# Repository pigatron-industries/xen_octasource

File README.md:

# OctaSource

A Eurorack synthesiser module with 8 control voltage outputs.

[Documentation](https://pigatron-industries.github.io/xen_octasource/)

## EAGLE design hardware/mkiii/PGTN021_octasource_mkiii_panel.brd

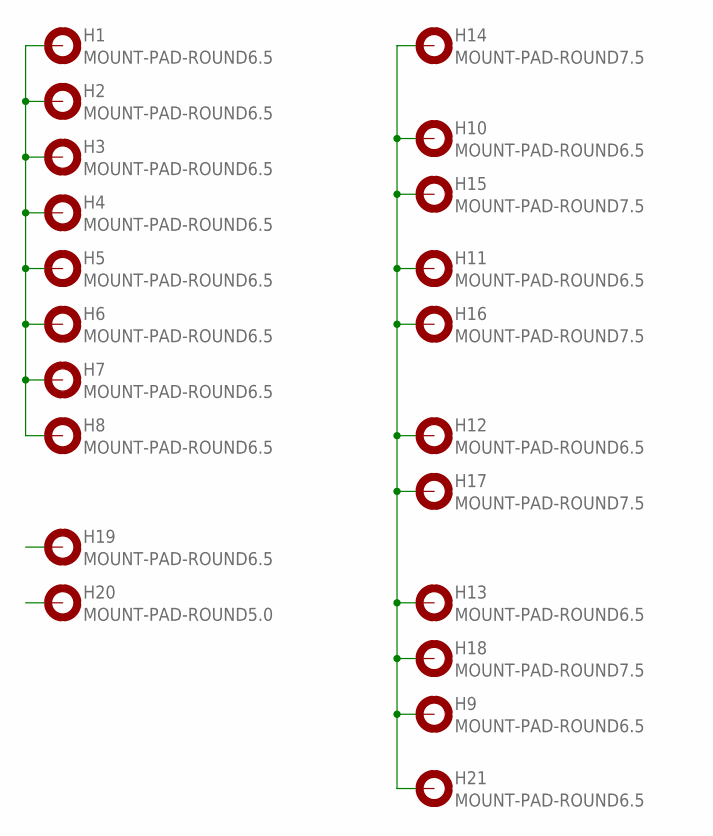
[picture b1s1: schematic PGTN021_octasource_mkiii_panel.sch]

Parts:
H1, H2, H3, H4, H5, H6, H7, H8, H9, H10, H11, H12, H13, H19, H21: MOUNT-PAD-ROUND6.5; 6.5-PAD
H14, H15, H16, H17, H18: MOUNT-PAD-ROUND7.5; 7.5-PAD
H20: MOUNT-PAD-ROUND5.0; 5,0-PAD

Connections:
unnamed: H9.B6.5, H10.B6.5, H11.B6.5, H12.B6.5, H13.B6.5, H14.B7.5, H15.B7.5, H16.B7.5, H17.B7.5, H18.B7.5, H21.B6.5
unnamed: H1.B6.5, H2.B6.5, H3.B6.5, H4.B6.5, H5.B6.5, H6.B6.5, H7.B6.5, H8.B6.5

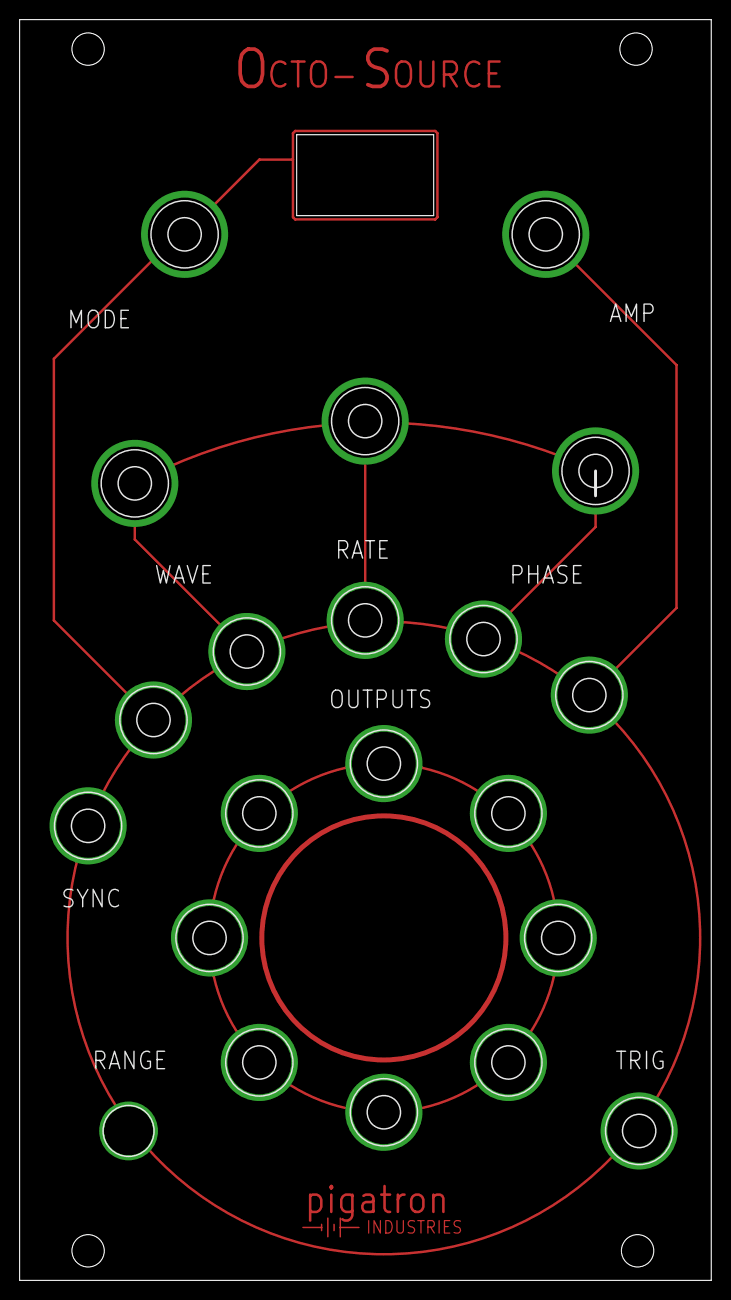
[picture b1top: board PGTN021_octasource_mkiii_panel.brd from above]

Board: 2 copper layers, 70.5 x 128.6 mm, 26 parts (0 on the bottom side), 2 nets.

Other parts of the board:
U$1, U$3, U$4, U$5: 3,3
U$2: PIGATRON-LOGO-TRACE

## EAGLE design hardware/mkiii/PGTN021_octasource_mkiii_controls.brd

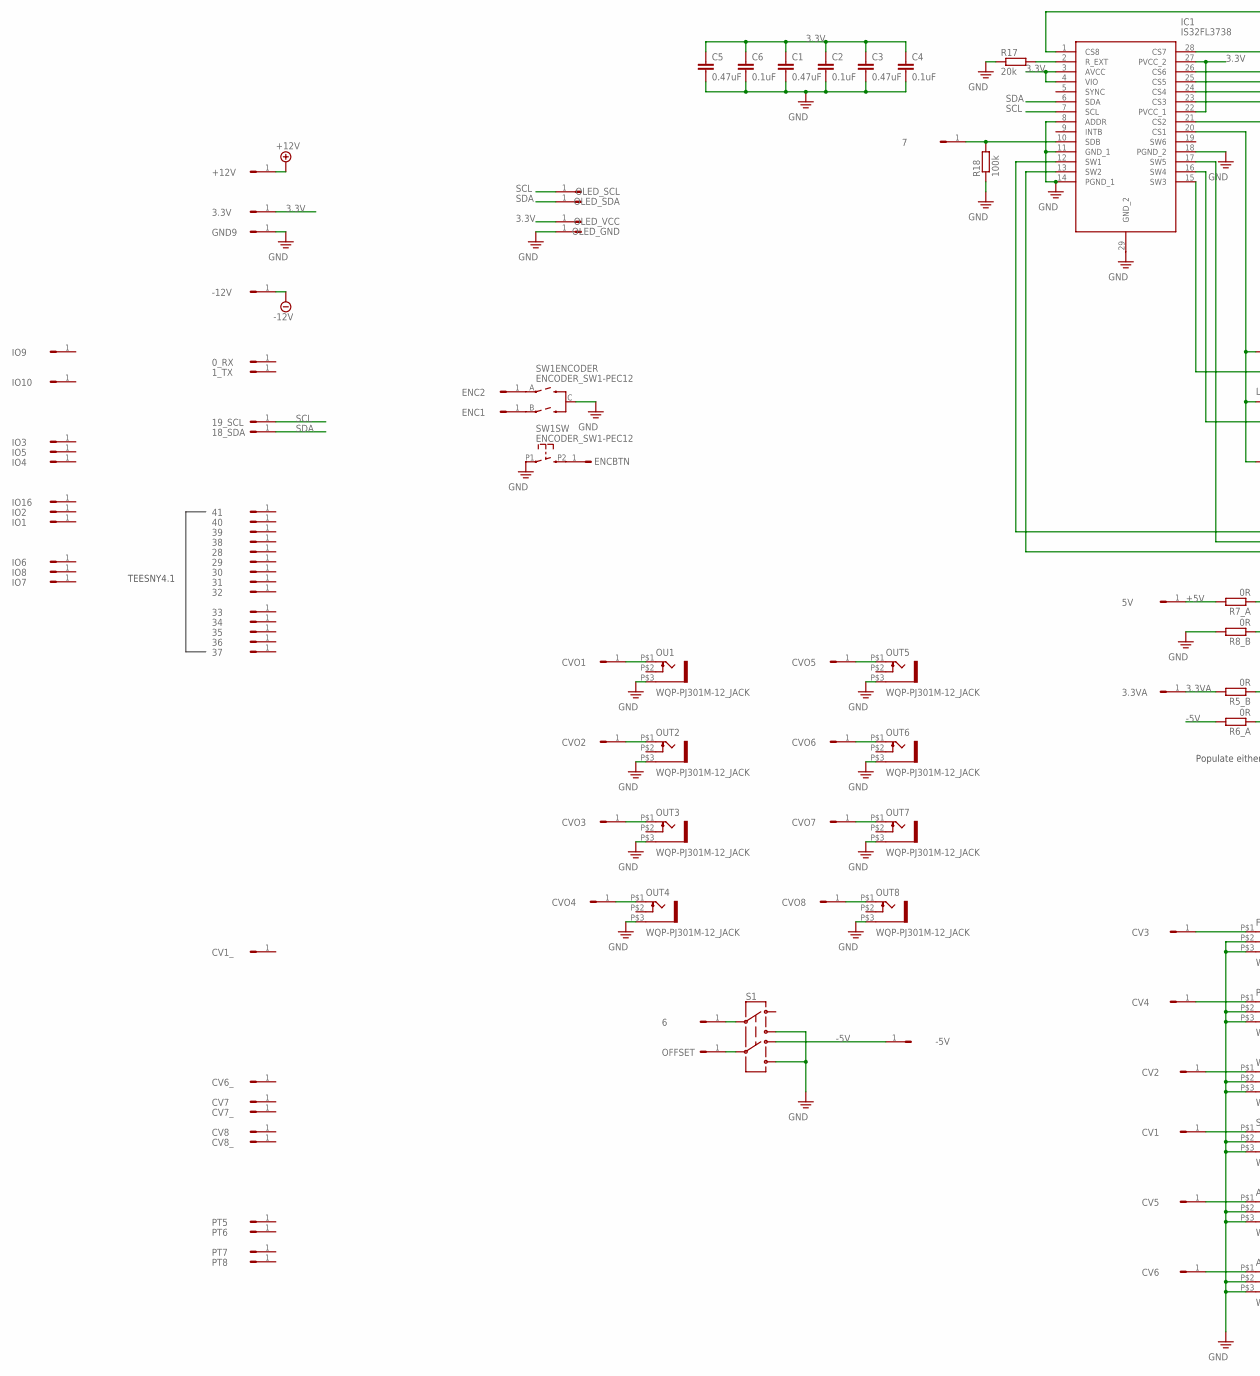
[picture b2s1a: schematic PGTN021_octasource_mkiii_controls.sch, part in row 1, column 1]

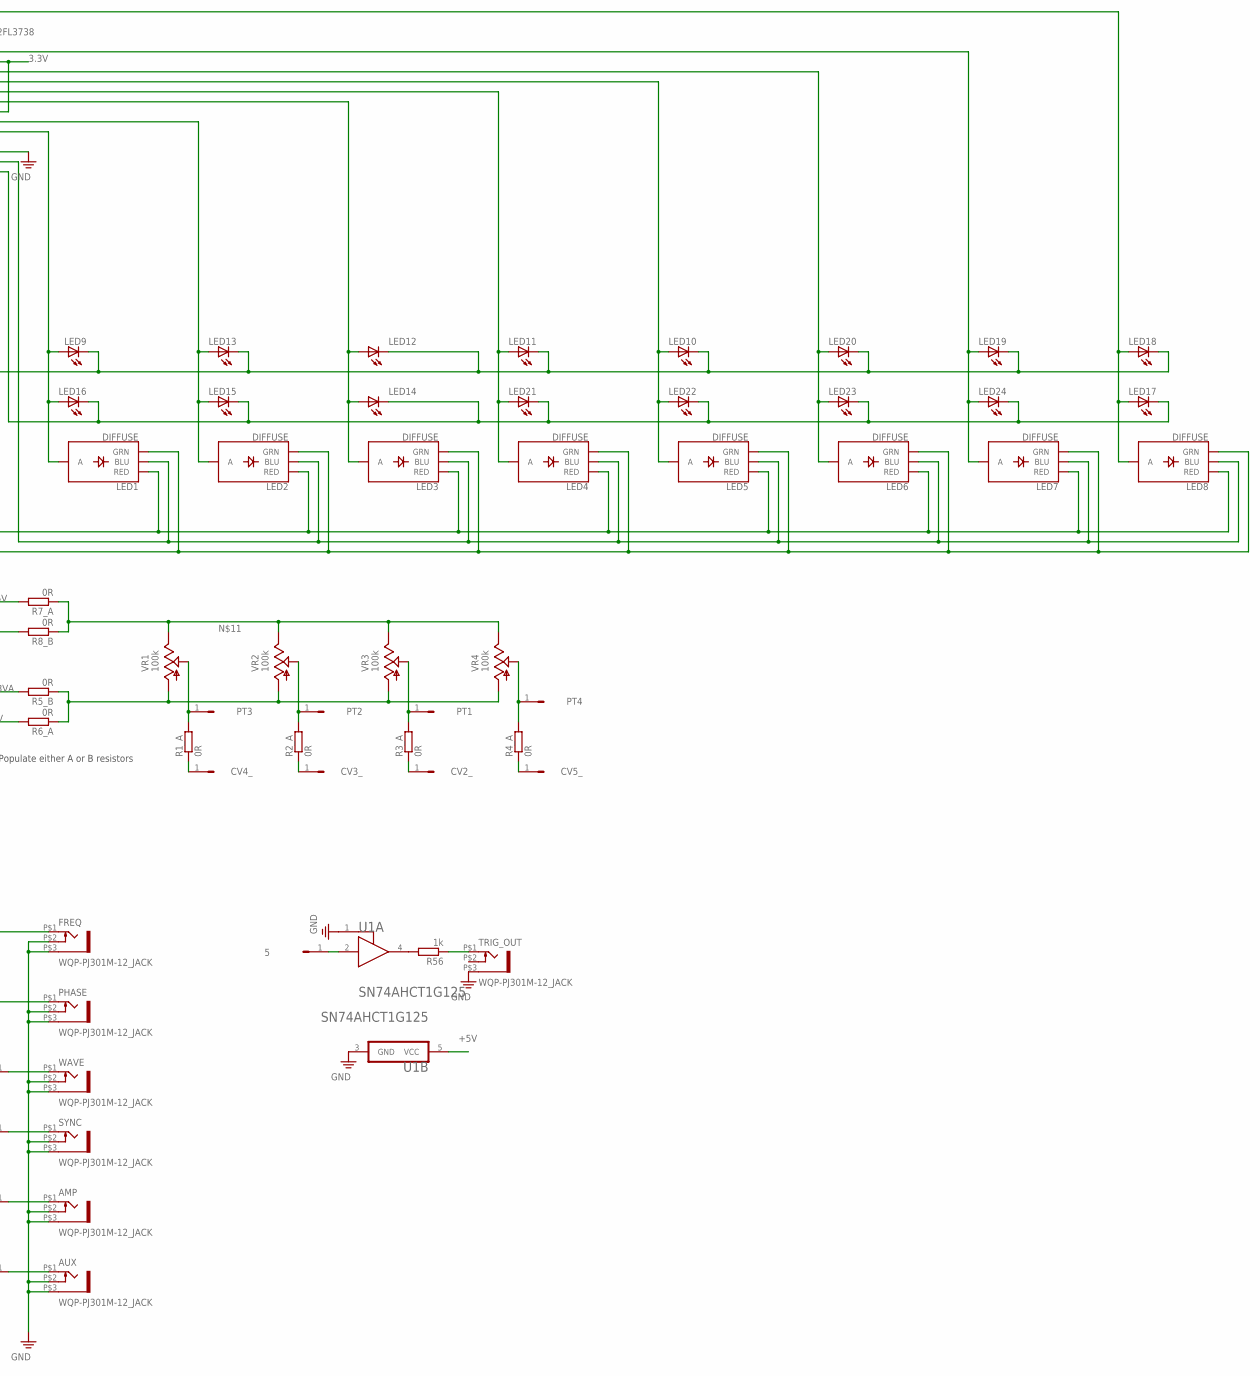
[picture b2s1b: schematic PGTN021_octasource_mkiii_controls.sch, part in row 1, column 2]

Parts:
0_RX, 1_TX, 3.3V, 3.3VA, 5, 5V, 6, 7, 18_SDA, 19_SCL, 28, 29, 30, 31, 32, 33, 34, 35, 36, 37, 38, 39, 40, 41: HEADER/MALE/01
+12V: HEADER/MALE/01
-5V, -12V: HEADER/MALE/01
AMP: WQP-PJ301M-12_JACK
AUX: WQP-PJ301M-12_JACK
C1, C3, C5: 0.47uF; C0603
C2, C4, C6: 0.1uF; C0603
CV1, CV1_, CV2, CV2_, CV3, CV3_, CV4, CV4_, CV5, CV5_, CV6, CV6_, CV7, CV7_, CV8, CV8_: HEADER/MALE/01
CVO1, CVO2, CVO3, CVO4, CVO5, CVO6, CVO7, CVO8: HEADER/MALE/01
ENC1, ENC2: HEADER/MALE/01
ENCBTN: HEADER/MALE/01
FREQ: WQP-PJ301M-12_JACK
GND9: HEADER/MALE/01
IC1: IS32FL3738; TSSOP29
IO1, IO2, IO3, IO4, IO5, IO6, IO7, IO8, IO9, IO10, IO16: HEADER/MALE/01
LED1, LED2, LED3, LED4, LED5, LED6, LED7, LED8: DIFFUSE; LED-RGB-THRU
LED9, LED10, LED11, LED12, LED13, LED14, LED15, LED16, LED17, LED18, LED19, LED20, LED21, LED22, LED23, LED24: LEDCHIPLED_0805; CHIPLED_0805
OFFSET: HEADER/MALE/01
OLED_GND: HEADER/MALE/01
OLED_SCL: HEADER/MALE/01
OLED_SDA: HEADER/MALE/01
OLED_VCC: HEADER/MALE/01
OU1: WQP-PJ301M-12_JACK
OUT2, OUT3, OUT4, OUT5, OUT6, OUT7, OUT8: WQP-PJ301M-12_JACK
PHASE: WQP-PJ301M-12_JACK
PT1, PT2, PT3, PT4, PT5, PT6, PT7, PT8: HEADER/MALE/01
R1_A, R2_A, R3_A, R4_A, R5_B, R6_A, R7_A, R8_B: 0R; R0603
R17: 20k; R0603
R18: 100k; R0603
R56: 1k; R0603
S1: SWITCH-DPDTPTH2; SWITCH-DPDT_SUB_ROUND
SW1: ENCODER_SW1-PEC12; PEC12_INCREMENTAL_ENCODER
SYNC: WQP-PJ301M-12_JACK
TRIG_OUT: WQP-PJ301M-12_JACK
U1: 74AHCT1G125
VR1, VR2, VR3, VR4: 100k; 9MM_SNAP-IN_POT
WAVE: WQP-PJ301M-12_JACK

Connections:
3.3V: 3.3V.1, C1.1, C2.1, C3.1, C4.1, C5.1, C6.1, IC1.3 (AVCC), IC1.4 (VIO), IC1.22 (PVCC_1), IC1.27 (PVCC_2), OLED_VCC.1
3.3VA: 3.3VA.1, R5_B.2
+5V: 5V.1, R7_A.2, U1.5 (VCC)
+12V: +12V.1
-5V: -5V.1, R6_A.2, S1.4
-12V: -12V.1
unnamed: IC1.12 (SW1), LED1.1 (RED), LED2.1 (RED), LED3.1 (RED), LED4.1 (RED), LED5.1 (RED), LED6.1 (RED), LED7.1 (RED), LED8.1 (RED)
unnamed: PT3.1, R1_A.2, VR1.2 (S)
unnamed: IC1.17 (SW5), LED1.4 (BLU), LED2.4 (BLU), LED3.4 (BLU), LED4.4 (BLU), LED5.4 (BLU), LED6.4 (BLU), LED7.4 (BLU), LED8.4 (BLU)
unnamed: CVO1.1, OU1.P$1 (2)
unnamed: 6.1, S1.2
unnamed: IC1.13 (SW2), LED1.3 (GRN), LED2.3 (GRN), LED3.3 (GRN), LED4.3 (GRN), LED5.3 (GRN), LED6.3 (GRN), LED7.3 (GRN), LED8.3 (GRN)
unnamed: PT2.1, R2_A.2, VR2.2 (S)
unnamed: CVO2.1, OUT2.P$1 (2)
unnamed: PT1.1, R3_A.2, VR3.2 (S)
unnamed: PT4.1, R4_A.2, VR4.2 (S)
unnamed: R7_A.1, R8_B.1, VR1.3 (E), VR2.3 (E), VR3.3 (E), VR4.3 (E)
unnamed: CVO3.1, OUT3.P$1 (2)
unnamed: OFFSET.1, S1.5
unnamed: AUX.P$1 (2), CV6.1
unnamed: CV4_.1, R1_A.1
unnamed: CVO4.1, OUT4.P$1 (2)
unnamed: CV3_.1, R2_A.1
unnamed: CV2_.1, R3_A.1
unnamed: CV5_.1, R4_A.1
unnamed: CVO5.1, OUT5.P$1 (2)
unnamed: R5_B.1, R6_A.1, VR1.1 (A), VR2.1 (A), VR3.1 (A), VR4.1 (A)
unnamed: CVO6.1, OUT6.P$1 (2)
unnamed: CVO7.1, OUT7.P$1 (2)
unnamed: CVO8.1, OUT8.P$1 (2)
unnamed: 7.1, IC1.10 (SDB), R18.2
unnamed: R56.2, U1.4 (Y)
unnamed: 5.1, U1.2 (A)
unnamed: ENCBTN.1, SW1.P2 (2)
unnamed: ENC2.1, SW1.A
unnamed: ENC1.1, SW1.B
unnamed: CV1.1, SYNC.P$1 (2)
unnamed: CV2.1, WAVE.P$1 (2)
unnamed: CV3.1, FREQ.P$1 (2)
unnamed: CV4.1, PHASE.P$1 (2)
unnamed: AMP.P$1 (2), CV5.1
unnamed: R56.1, TRIG_OUT.P$1 (2)
unnamed: IC1.20 (CS1), LED1.2 (A), LED9.A, LED16.A
unnamed: IC1.21 (CS2), LED2.2 (A), LED13.A, LED15.A
unnamed: IC1.23 (CS3), LED3.2 (A), LED12.A, LED14.A
unnamed: IC1.16 (SW4), LED14.C, LED15.C, LED16.C, LED17.C, LED21.C, LED22.C, LED23.C, LED24.C
unnamed: IC1.15 (SW3), LED9.C, LED10.C, LED11.C, LED12.C, LED13.C, LED18.C, LED19.C, LED20.C
unnamed: IC1.24 (CS4), LED4.2 (A), LED11.A, LED21.A
unnamed: IC1.25 (CS5), LED5.2 (A), LED10.A, LED22.A
unnamed: IC1.26 (CS6), LED6.2 (A), LED20.A, LED23.A
unnamed: IC1.28 (CS7), LED7.2 (A), LED19.A, LED24.A
unnamed: IC1.1 (CS8), LED8.2 (A), LED17.A, LED18.A
unnamed: IC1.2 (R_EXT), R17.2
PE: AMP.P$2 (3), AMP.P$3 (1), AUX.P$2 (3), AUX.P$3 (1), C1.2, C2.2, C3.2, C4.2, C5.2, C6.2, FREQ.P$2 (3), FREQ.P$3 (1), GND9.1, IC1.8 (ADDR), IC1.11 (GND_1), IC1.14 (PGND_1), IC1.18 (PGND_2), IC1.29 (GND_2), OLED_GND.1, OU1.P$3 (1), OUT2.P$3 (1), OUT3.P$3 (1), OUT4.P$3 (1), OUT5.P$3 (1), OUT6.P$3 (1), OUT7.P$3 (1), OUT8.P$3 (1), PHASE.P$2 (3), PHASE.P$3 (1), R8_B.2, R17.1, R18.1, S1.3, S1.6, SW1.C, SW1.P1 (1), SYNC.P$2 (3), SYNC.P$3 (1), TRIG_OUT.P$3 (1), U1.1 (!OE!), U1.3 (GND), WAVE.P$2 (3), WAVE.P$3 (1)
SCL: 19_SCL.1, IC1.7 (SCL), OLED_SCL.1
SDA: 18_SDA.1, IC1.6 (SDA), OLED_SDA.1

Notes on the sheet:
TEESNY4.1
Populate either A or B resistors

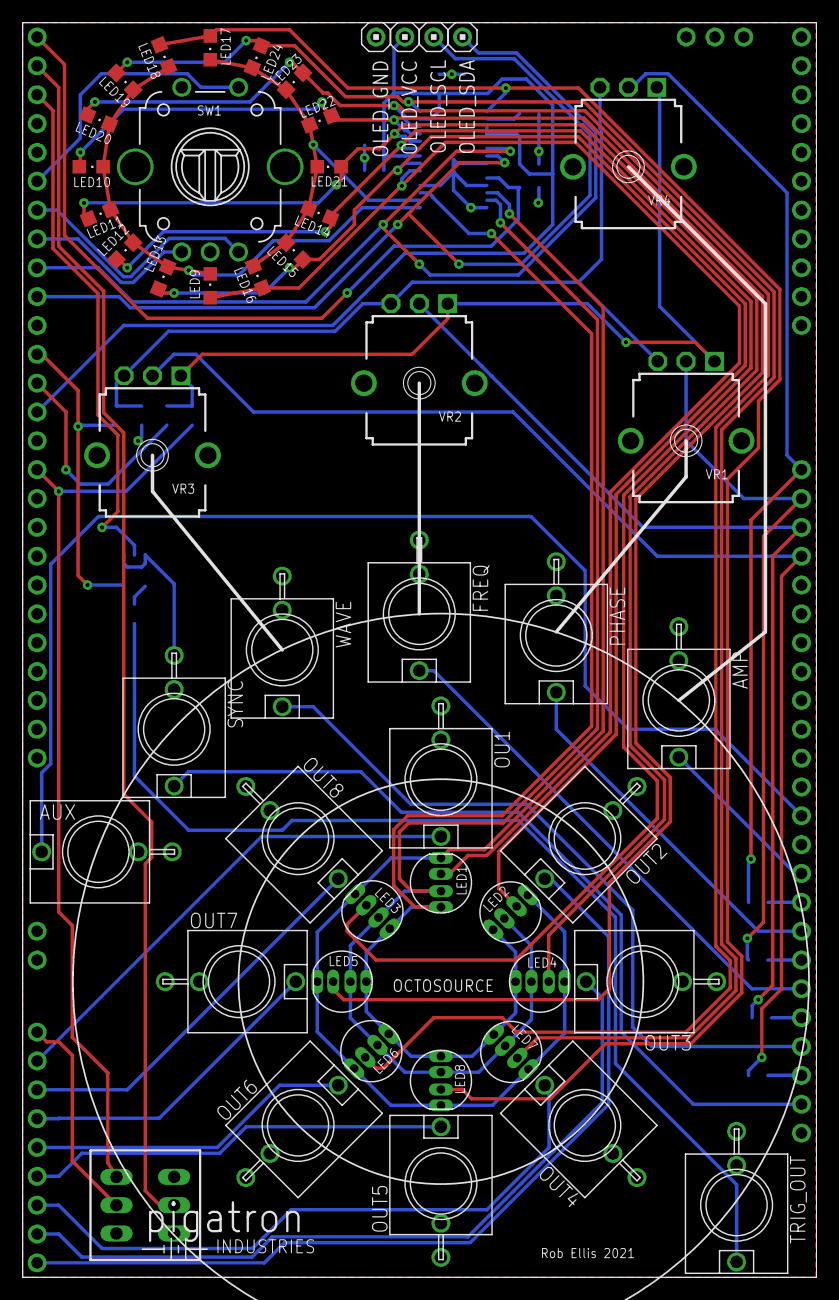
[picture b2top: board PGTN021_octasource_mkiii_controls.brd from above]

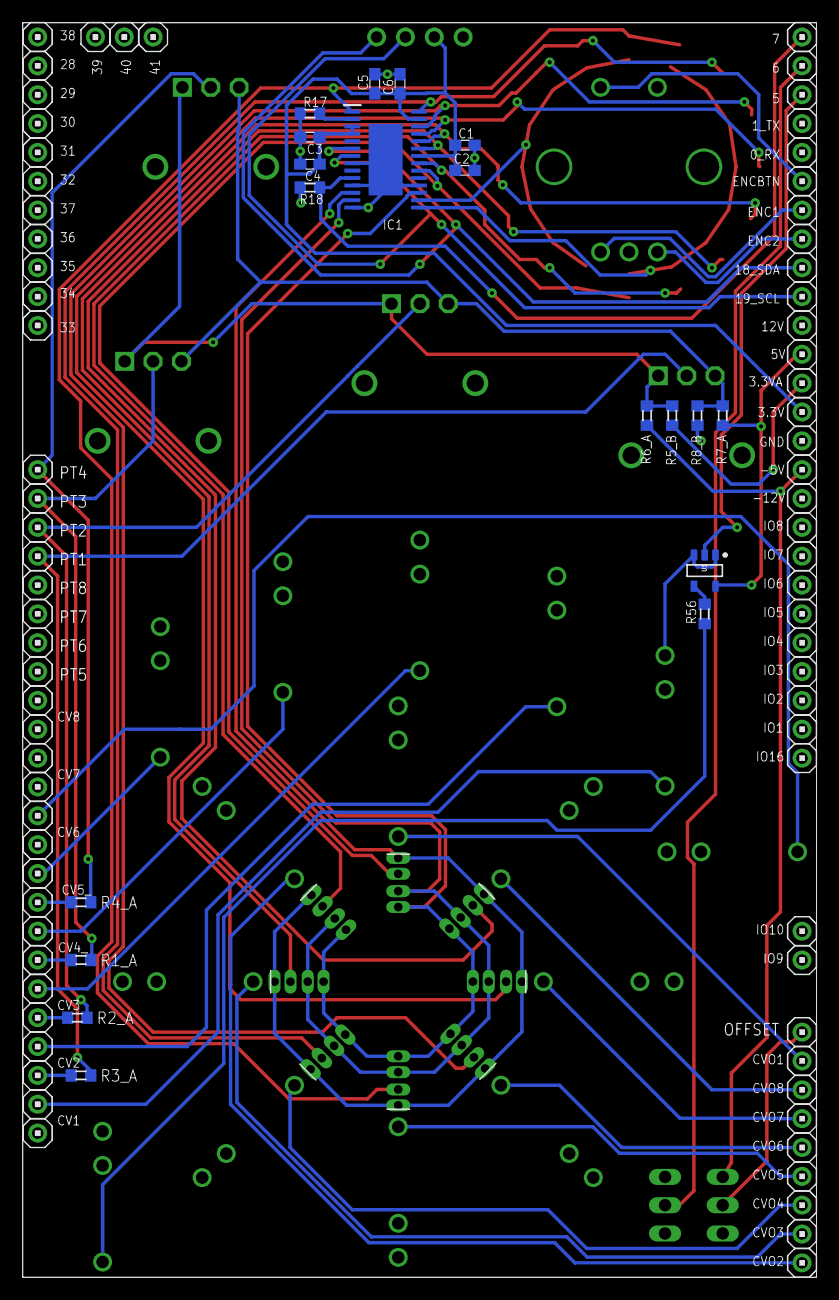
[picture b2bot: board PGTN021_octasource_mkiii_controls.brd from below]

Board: 2 copper layers, 69.9 x 110.5 mm, 144 parts (94 on the bottom side), 54 nets.

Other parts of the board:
U$1: PIGATRON-LOGO

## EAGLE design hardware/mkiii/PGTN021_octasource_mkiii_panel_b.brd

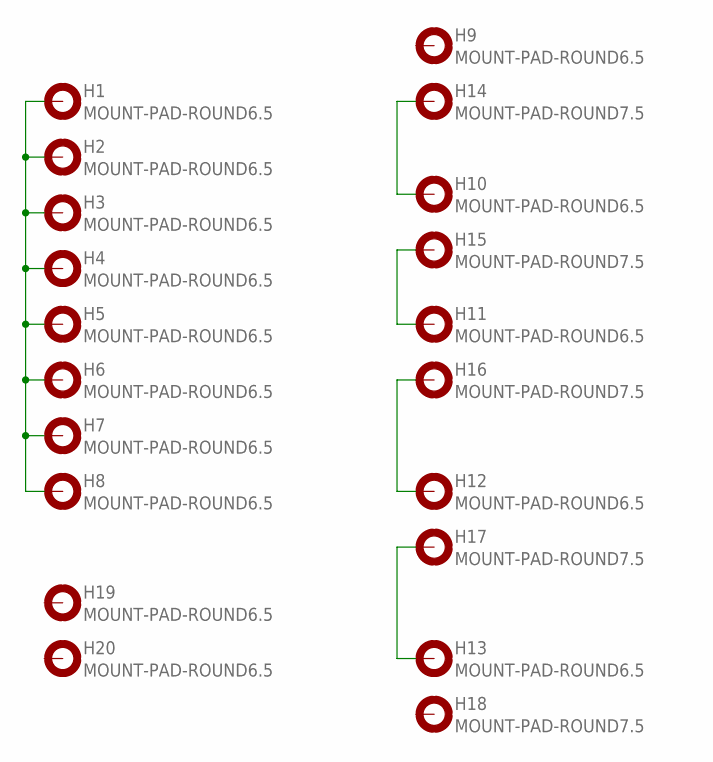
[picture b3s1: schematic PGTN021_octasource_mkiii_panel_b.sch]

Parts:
H1, H2, H3, H4, H5, H6, H7, H8, H9, H10, H11, H12, H13, H19, H20: MOUNT-PAD-ROUND6.5; 6.5-PAD
H14, H15, H16, H17, H18: MOUNT-PAD-ROUND7.5; 7.5-PAD

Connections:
unnamed: H1.B6.5, H2.B6.5, H3.B6.5, H4.B6.5, H5.B6.5, H6.B6.5, H7.B6.5, H8.B6.5
unnamed: H10.B6.5, H14.B7.5
unnamed: H11.B6.5, H15.B7.5
unnamed: H12.B6.5, H16.B7.5
unnamed: H13.B6.5, H17.B7.5

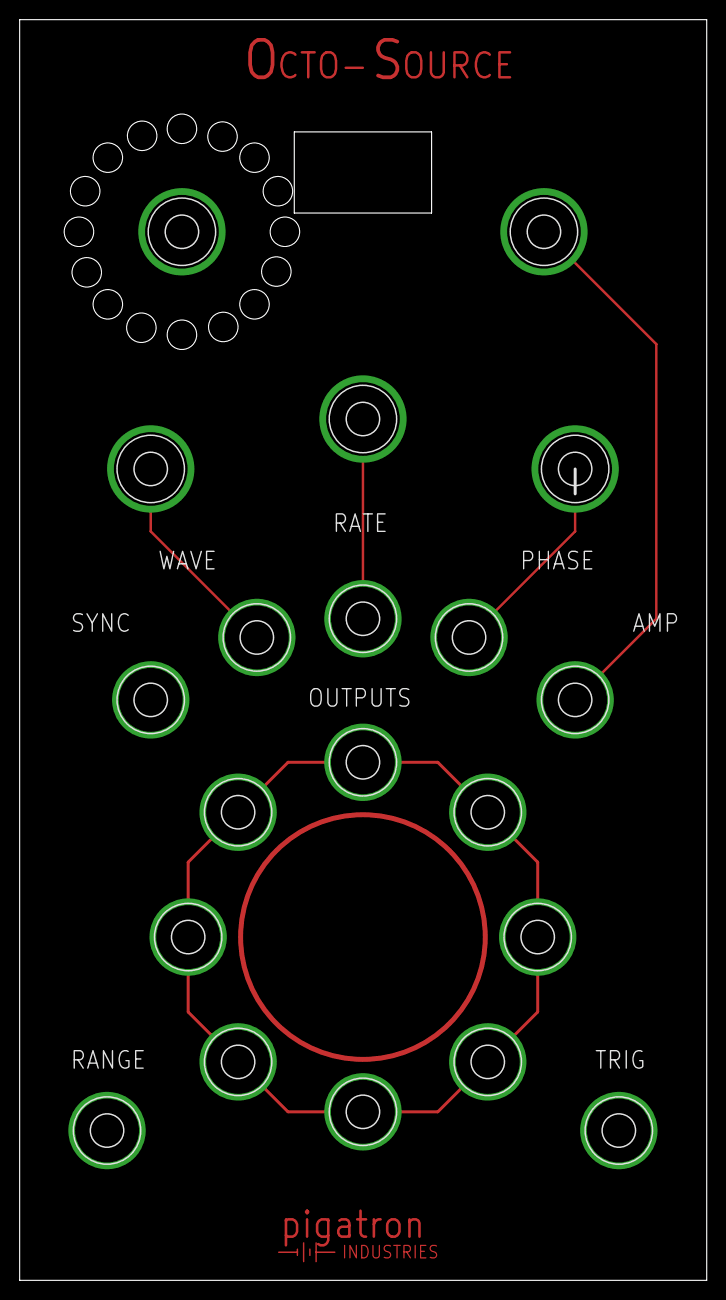
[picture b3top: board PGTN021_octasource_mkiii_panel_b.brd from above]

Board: 2 copper layers, 69.9 x 128.3 mm, 21 parts (0 on the bottom side), 5 nets.

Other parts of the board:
U$2: PIGATRON-LOGO-TRACE

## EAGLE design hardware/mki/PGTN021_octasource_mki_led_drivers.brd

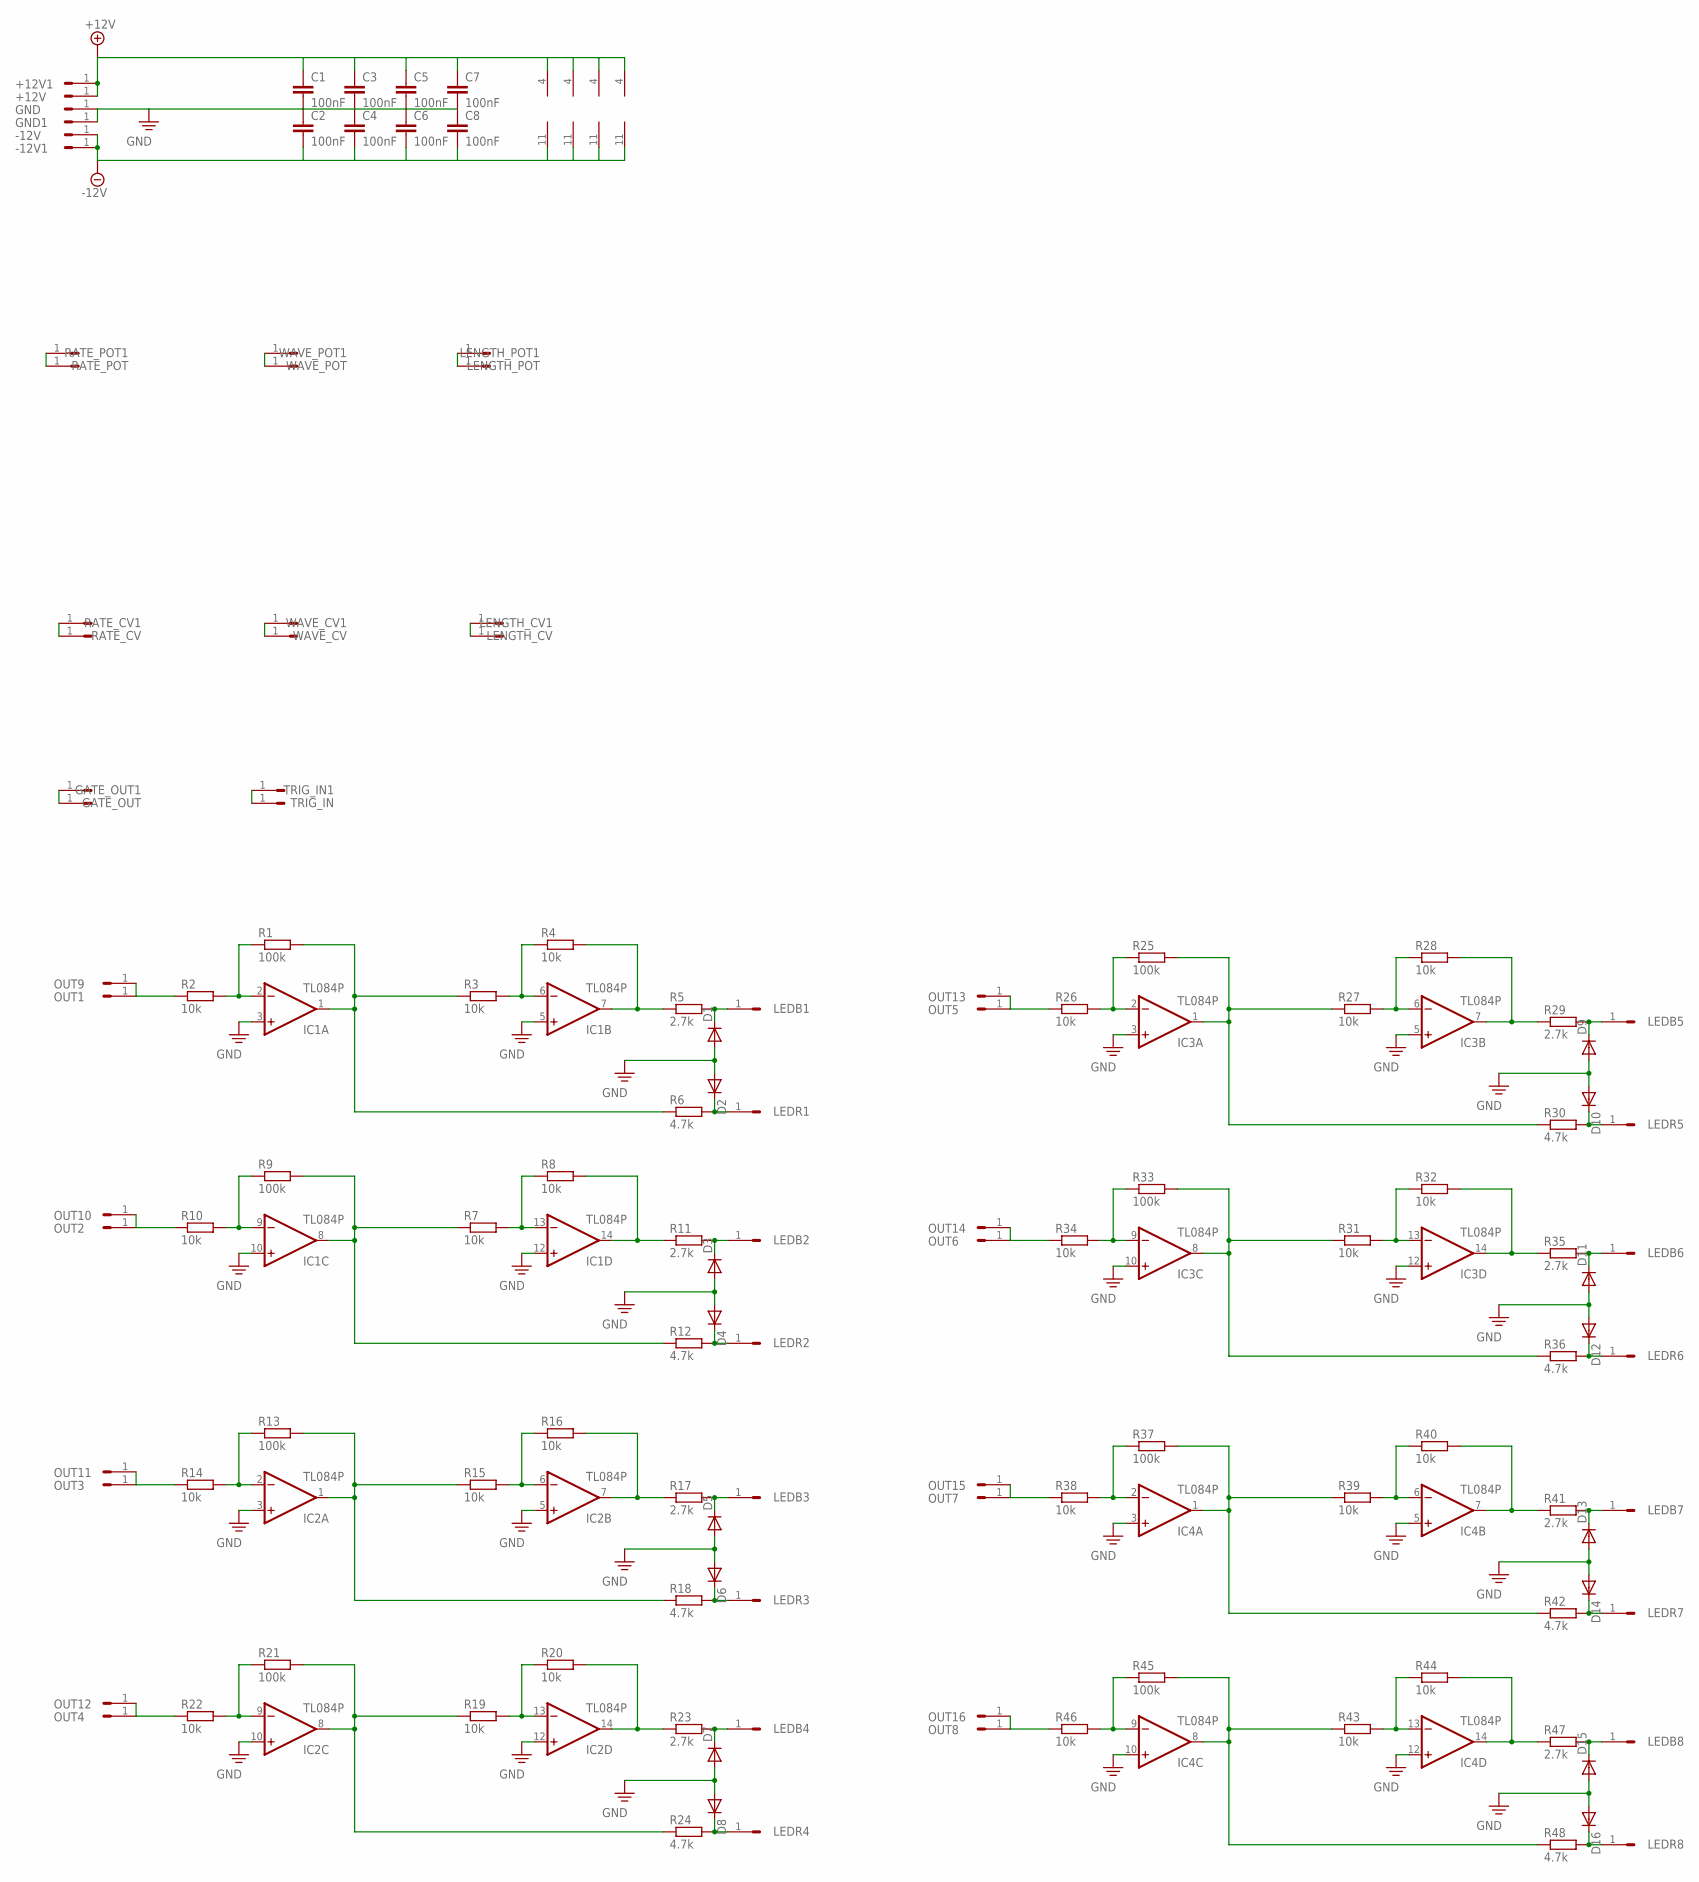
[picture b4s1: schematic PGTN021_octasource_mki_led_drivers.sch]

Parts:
+12V, +12V1: HEADER/MALE/01
-12V, -12V1: HEADER/MALE/01
C1, C2, C3, C4, C5, C6, C7, C8: 100nF; CERAMICDISC/5
D1, D2, D3, D4, D5, D6, D7, D8, D9, D10, D11, D12, D13, D14, D15, D16: 1N4148DO35-7; DO35-7
GATE_OUT, GATE_OUT1: HEADER/MALE/01
GND, GND1: HEADER/MALE/01
IC1, IC2, IC3, IC4: TL084P; DIL14
LEDB1, LEDB2, LEDB3, LEDB4, LEDB5, LEDB6, LEDB7, LEDB8: HEADER/MALE/01
LEDR1, LEDR2, LEDR3, LEDR4, LEDR5, LEDR6, LEDR7, LEDR8: HEADER/MALE/01
LENGTH_CV, LENGTH_CV1: HEADER/MALE/01
LENGTH_POT, LENGTH_POT1: HEADER/MALE/01
OUT1, OUT2, OUT3, OUT4, OUT5, OUT6, OUT7, OUT8, OUT9, OUT10, OUT11, OUT12, OUT13, OUT14, OUT15, OUT16: HEADER/MALE/01
R1, R9, R13, R21, R25, R33, R37, R45: 100k; RESISTOR/7.5
R2, R3, R4, R7, R8, R10, R14, R15, R16, R19, R20, R22, R26, R27, R28, R31, R32, R34, R38, R39, R40, R43, R44, R46: 10k; RESISTOR/7.5
R5, R11, R17, R23, R29, R35, R41, R47: 2.7k; RESISTOR/7.5
R6, R12, R18, R24, R30, R36, R42, R48: 4.7k; RESISTOR/7.5
RATE_CV, RATE_CV1: HEADER/MALE/01
RATE_POT, RATE_POT1: HEADER/MALE/01
TRIG_IN, TRIG_IN1: HEADER/MALE/01
WAVE_CV, WAVE_CV1: HEADER/MALE/01
WAVE_POT, WAVE_POT1: HEADER/MALE/01

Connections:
+12V: +12V.1, +12V1.1, C1.1, C3.1, C5.1, C7.1, IC1.4 (V+), IC2.4 (V+), IC3.4 (V+), IC4.4 (V+)
-12V: -12V.1, -12V1.1, C2.2, C4.2, C6.2, C8.2, IC1.11 (V-), IC2.11 (V-), IC3.11 (V-), IC4.11 (V-)
unnamed: IC1.6 (-IN), R3.2, R4.1
unnamed: IC1.2 (-IN), R1.1, R2.2
unnamed: IC1.1 (OUT), R1.2, R3.1, R6.1
unnamed: OUT1.1, OUT9.1, R2.1
unnamed: IC1.7 (OUT), R4.2, R5.1
unnamed: D1.C, LEDB1.1, R5.2
unnamed: D2.C, LEDR1.1, R6.2
unnamed: IC1.13 (-IN), R7.2, R8.1
unnamed: IC1.9 (-IN), R9.1, R10.2
unnamed: OUT2.1, OUT10.1, R10.1
unnamed: IC1.14 (OUT), R8.2, R11.1
unnamed: IC1.8 (OUT), R7.1, R9.2, R12.1
unnamed: IC2.2 (-IN), R13.1, R14.2
unnamed: D3.C, LEDB2.1, R11.2
unnamed: D4.C, LEDR2.1, R12.2
unnamed: IC2.1 (OUT), R13.2, R15.1, R18.1
unnamed: IC2.6 (-IN), R15.2, R16.1
unnamed: OUT3.1, OUT11.1, R14.1
unnamed: IC2.7 (OUT), R16.2, R17.1
unnamed: D5.C, LEDB3.1, R17.2
unnamed: D6.C, LEDR3.1, R18.2
unnamed: IC2.13 (-IN), R19.2, R20.1
unnamed: IC2.9 (-IN), R21.1, R22.2
unnamed: IC2.14 (OUT), R20.2, R23.1
unnamed: IC2.8 (OUT), R19.1, R21.2, R24.1
unnamed: D7.C, LEDB4.1, R23.2
unnamed: D8.C, LEDR4.1, R24.2
unnamed: OUT4.1, OUT12.1, R22.1
unnamed: IC3.2 (-IN), R25.1, R26.2
unnamed: IC3.1 (OUT), R25.2, R27.1, R30.1
unnamed: IC3.6 (-IN), R27.2, R28.1
unnamed: OUT5.1, OUT13.1, R26.1
unnamed: IC3.7 (OUT), R28.2, R29.1
unnamed: D9.C, LEDB5.1, R29.2
unnamed: D10.C, LEDR5.1, R30.2
unnamed: IC3.13 (-IN), R31.2, R32.1
unnamed: IC3.9 (-IN), R33.1, R34.2
unnamed: IC3.14 (OUT), R32.2, R35.1
unnamed: IC3.8 (OUT), R31.1, R33.2, R36.1
unnamed: D11.C, LEDB6.1, R35.2
unnamed: D12.C, LEDR6.1, R36.2
unnamed: OUT6.1, OUT14.1, R34.1
unnamed: RATE_POT.1, RATE_POT1.1
unnamed: IC4.2 (-IN), R37.1, R38.2
unnamed: IC4.1 (OUT), R37.2, R39.1, R42.1
unnamed: IC4.6 (-IN), R39.2, R40.1
unnamed: OUT7.1, OUT15.1, R38.1
unnamed: IC4.7 (OUT), R40.2, R41.1
unnamed: D13.C, LEDB7.1, R41.2
unnamed: D14.C, LEDR7.1, R42.2
unnamed: IC4.13 (-IN), R43.2, R44.1
unnamed: IC4.9 (-IN), R45.1, R46.2
unnamed: IC4.14 (OUT), R44.2, R47.1
unnamed: IC4.8 (OUT), R43.1, R45.2, R48.1
unnamed: D15.C, LEDB8.1, R47.2
unnamed: D16.C, LEDR8.1, R48.2
unnamed: OUT8.1, OUT16.1, R46.1
unnamed: RATE_CV.1, RATE_CV1.1
unnamed: GATE_OUT.1, GATE_OUT1.1
unnamed: TRIG_IN.1, TRIG_IN1.1
unnamed: WAVE_CV.1, WAVE_CV1.1
unnamed: LENGTH_CV.1, LENGTH_CV1.1
unnamed: LENGTH_POT.1, LENGTH_POT1.1
unnamed: WAVE_POT.1, WAVE_POT1.1
PE: C1.2, C2.1, C3.2, C4.1, C5.2, C6.1, C7.2, C8.1, D1.A, D2.A, D3.A, D4.A, D5.A, D6.A, D7.A, D8.A, D9.A, D10.A, D11.A, D12.A, D13.A, D14.A, D15.A, D16.A, GND.1, GND1.1, IC1.3 (+IN), IC1.5 (+IN), IC1.10 (+IN), IC1.12 (+IN), IC2.3 (+IN), IC2.5 (+IN), IC2.10 (+IN), IC2.12 (+IN), IC3.3 (+IN), IC3.5 (+IN), IC3.10 (+IN), IC3.12 (+IN), IC4.3 (+IN), IC4.5 (+IN), IC4.10 (+IN), IC4.12 (+IN)

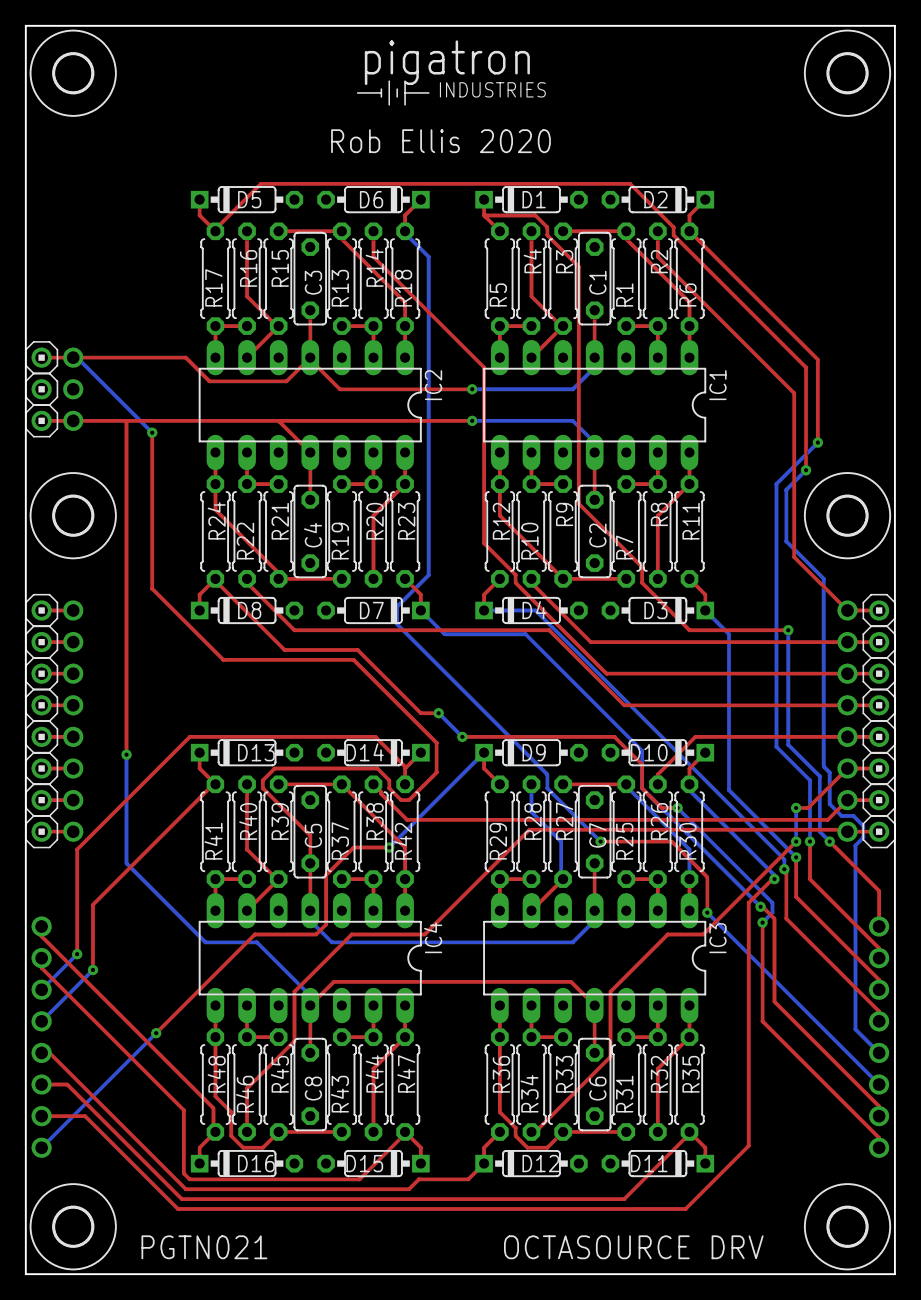
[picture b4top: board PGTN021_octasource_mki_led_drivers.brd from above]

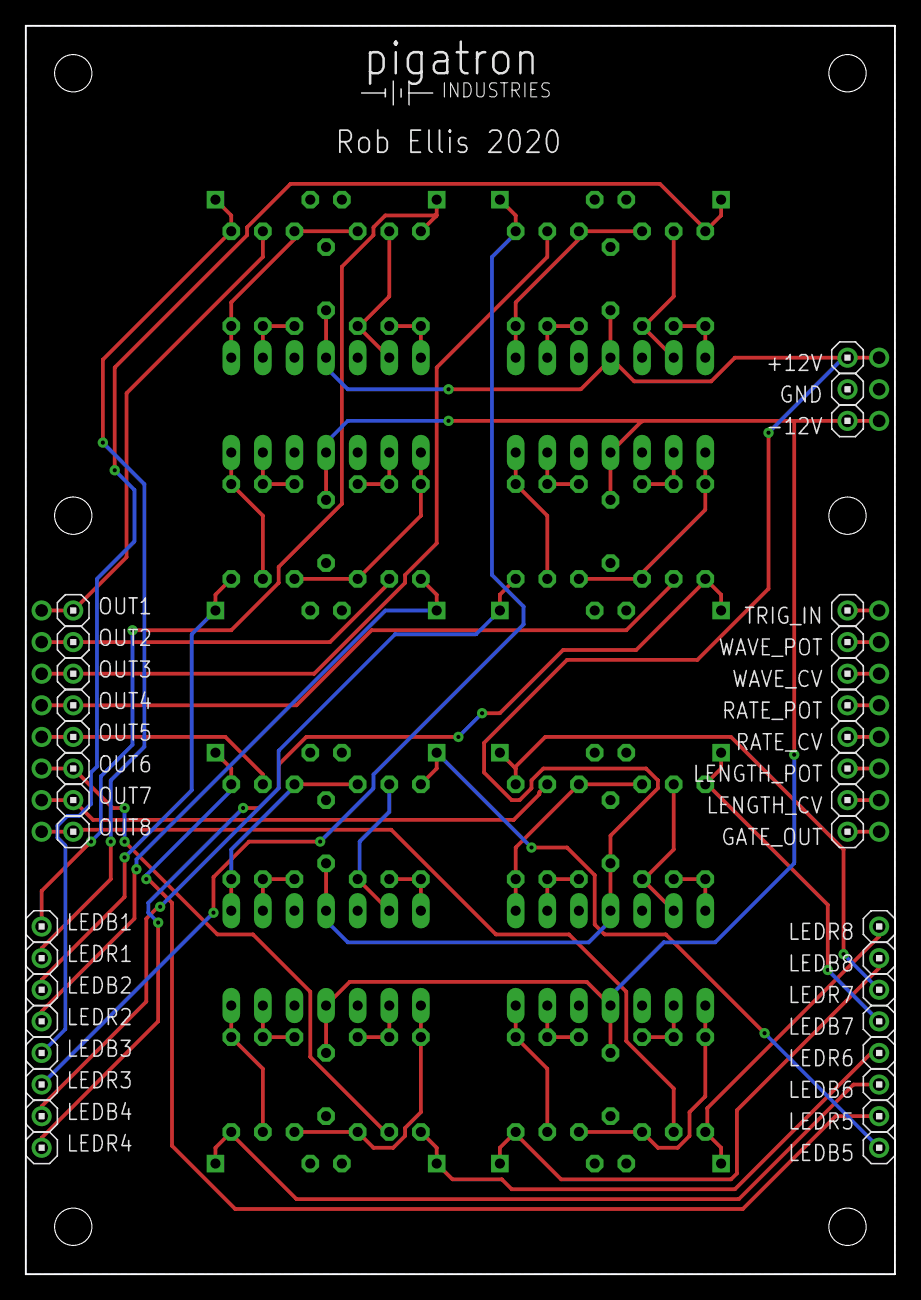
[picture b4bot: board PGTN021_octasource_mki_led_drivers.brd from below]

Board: 2 copper layers, 69.8 x 100.3 mm, 138 parts (36 on the bottom side), 67 nets.

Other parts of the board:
U$1, U$2: PIGATRON-LOGO
U$4, U$5, U$9, U$10, U$11, U$12: STANDOFF/3.0
